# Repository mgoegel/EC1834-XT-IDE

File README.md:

# XT-IDE 8-Bit IDE Controller for Robotron EC1834

[Deutsche Version](README-DE.md)

This is a modified version of the original Glitchworks XT-IDE rev 4 controller.

The ISA edge connector is replaced with DIN 41612 connector, used by the Robotron EC1834 PC.

Also the layout of the PCB was modified, to fit the mounting height.

Modification was done by Mario Goegel.

**IMPORTANT NOTES ON Rev 4b (Revision not printed)**

The idea to change the pull down resistors to pull up was an bad idea, as I did not saw all required changes.
The board will just not work, if assembled as planned.

Required changes:

* Pin 2 from RN2 has to be disconnected
* A 10K resistor needs to be connected on U1 pin 12 and GND (may be C1)
* The descriptions are not correct for SW2 ENA and WR - they match the original version, as they are not connected to RP2
* SW2 8K might be out of function - and 28C256 ROMs might not work. Untested, 82C64B are fine.

Fixed in revision 4c

**Disclaimer:**

I don't take responsibility for any damages resulting from these modifications. All changes have been made with the best of intentions and to the best of my knowledge.
Use on your own risk!

Original text from Glitchworks (modified):

[Glitch Works](http://www.glitchwrks.com/) continuing extension of the XT-IDE rev 2 ISA controller. This board, when used with a custom BIOS like the XT-IDE Universal BIOS, allows the use of modern 16-bit IDE devices on the 8-bit ISA bus.

More info on the Glitch Works project to provide boards, kits, and fully assembled units [can be found here](http://www.glitchwrks.com/xt-ide). A writeup on the rev 4 design process [is available here](http://www.glitchwrks.com/2017/11/23/xt-ide-rev4). 

Except for the DIN 41612 connector.

If you're looking for the rev 3 branch, [it can be found here](https://github.com/glitchwrks/xt_ide/tree/rev_3). The README and related documentation have been preserved along with the design files.

### Jumper Settings

[modem7](http://minuszerodegrees.net/) created a great set of jumper diagrams for the rev 4 boards, available [on his site](http://www.minuszerodegrees.net/xtide/rev_4/XT-IDE%20Rev%204%20-%20general.htm).

### Bill of Materials

You can find a BOM with Mouser part numbers [here](https://github.com/glitchwrks/xt_ide/blob/master/bill_of_materials.md). Do note that you can purchase complete parts kits from [The Glitch Works](http://www.glitchwrks.com/xt-ide) in addition to bare PC boards.

### Slot 8 Support

Completely removed in this version!

### Contributors

* Mario Goegel: Modification for EC1834
* Scott Christensen: inspriation 16-bit ATA interface for the 8-bit ISA bus
* Jeff Leyda/Hargle: original production board work, original BIOS work
* Andrew Lynch/N8VEM: layout work, initial group buy(s) on earlier revisions
* modem7: documentation, switch/jumper drawings

**Please contact me or send a pull request to get your name added to the list!**

There were no authors/contributors listed in the XT-IDE rev 2 schematics/board layout I started with. If you have contributed to this project and would like your name here, on the schematic, or on the board layout, please let me know. You can open an issue or submit a pull request.

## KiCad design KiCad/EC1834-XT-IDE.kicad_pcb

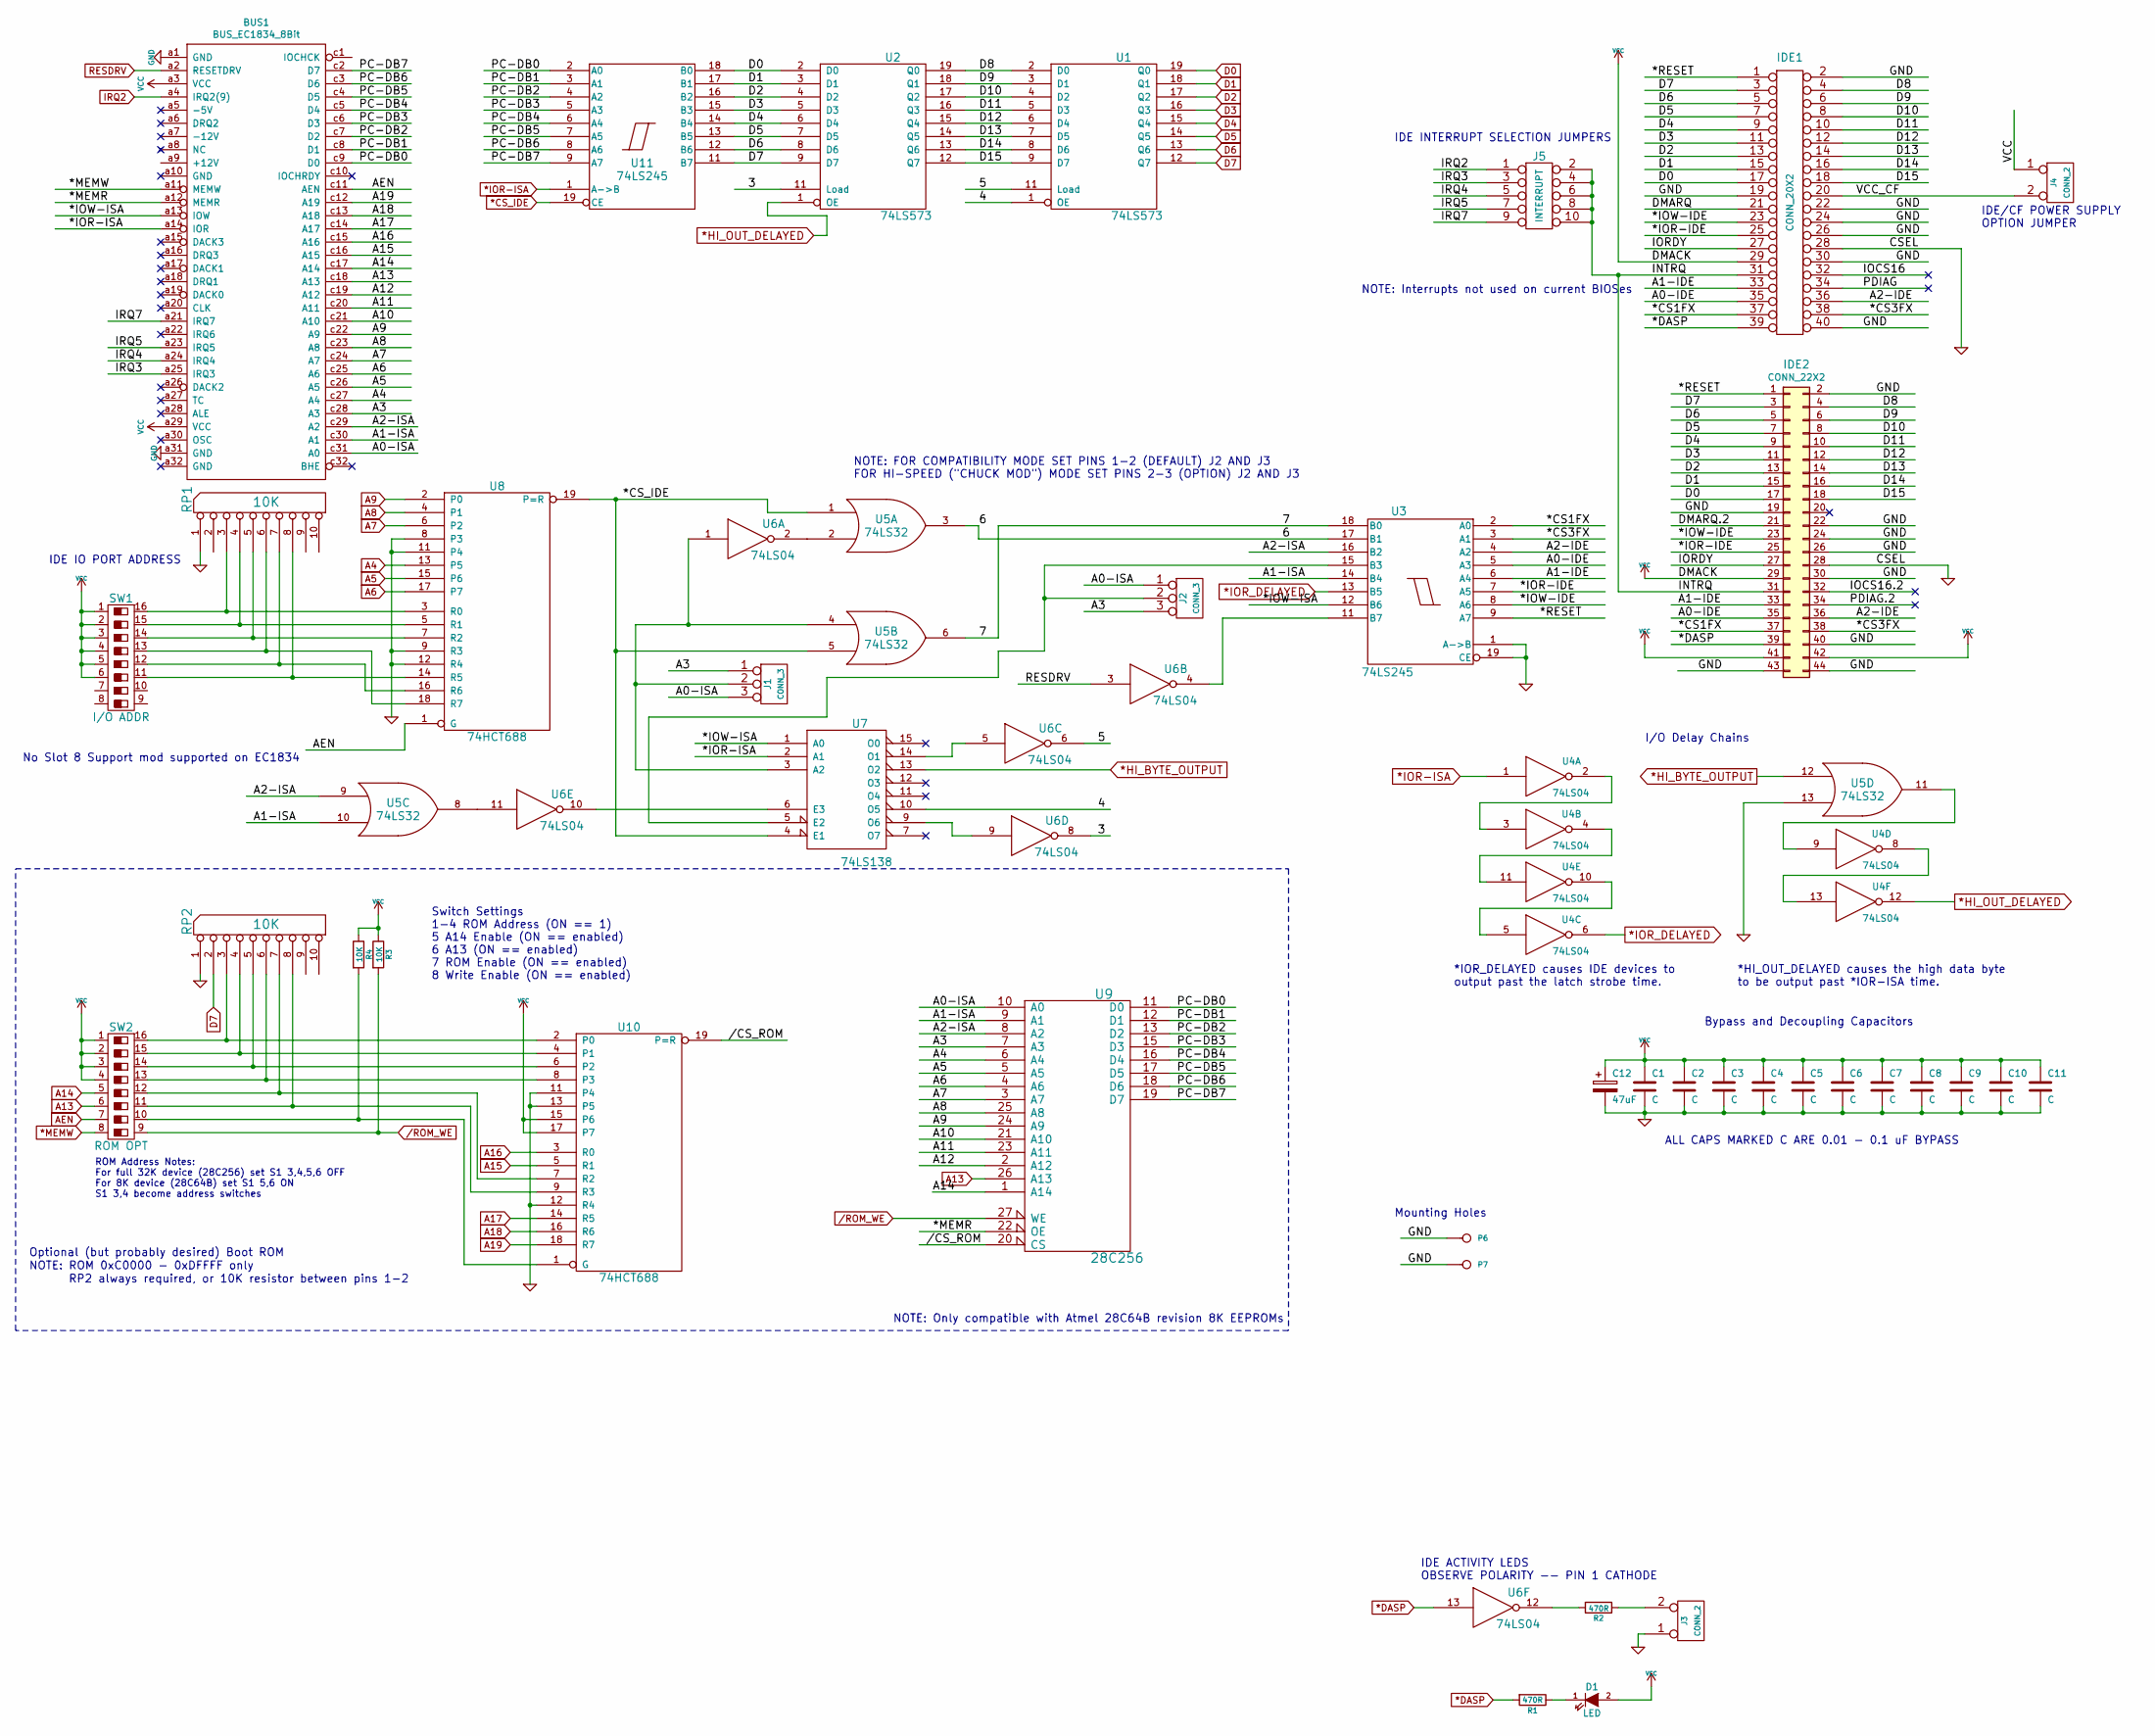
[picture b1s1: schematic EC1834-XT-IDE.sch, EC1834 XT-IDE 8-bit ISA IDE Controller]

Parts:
BUS1: BUS_EC1834_8Bit; DIN41612_C_3x32_Male_Horizontal_THT
C1, C2, C3, C4, C5, C6, C7, C8, C10, C11: C; AX_300
C9: C; AX_400
C12: 47uF; CP_RAD_250_100
D1: LED; LED-5MM
IDE1: CONN_20X2; STRAIGHT_2x20
IDE2: CONN_22X2; PinSocket_2x22_P2.00mm_Horizontal
J1, J2: CONN_3; 1x3
J3, J4: CONN_2; 1x2
J5: INTERRUPT; 5x2
P6, P7: CONN_1; 120mil_no_silkscreen
R1, R2: 470R; AX_400
R3, R4: 10K; AX_400
RP1, RP2: 10K; SIP10
SW1: I/O ADDR; DIP-16_300_OBROUND_NO_NOTCH
SW2: ROM OPT; DIP-16_300_OBROUND_NO_NOTCH
U1, U2: 74LS573; DIP-20_300_OBROUND
U3, U11: 74LS245; DIP-20_300_OBROUND
U4, U6: 74LS04; DIP-14_300_OBROUND
U5: 74LS32; DIP-14_300_OBROUND
U7: 74LS138; DIP-16_300_OBROUND
U8, U10: 74HCT688; DIP-20_300_OBROUND
U9: 28C256; DIP-28_600_OBROUND

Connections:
*CS_IDE: U5.1, U5.5, U7.4 (E1), U8.19 (P=R), U11.19 (CE)
*DASP: IDE1.39, IDE2.39, R1.2, U6.13
*HI_BYTE_OUTPUT: U5.12, U7.13 (O2)
*HI_OUT_DELAYED: U2.1 (OE), U4.12
*IOR-ISA: BUS1.a14 (IOR), U4.1, U7.2 (A1), U11.1 (A->B)
*IOR_DELAYED: U3.13 (B5), U4.6
*MEMW: BUS1.a11 (MEMW), SW2.8
/3: U2.11 (Load), U6.8
/4: U1.1 (OE), U7.10 (O5)
/5: U1.11 (Load), U6.6
/6: U3.17 (B1), U5.3
/7: U3.18 (B0), U5.6
/*CS1FX: IDE1.37, IDE2.37, U3.2 (A0)
/*CS3FX: IDE1.38, IDE2.38, U3.3 (A1)
/*IOR-IDE: IDE1.25, IDE2.25, U3.7 (A5)
/*IOW-IDE: IDE1.23, IDE2.23, U3.8 (A6)
/*IOW-ISA: BUS1.a13 (IOW), U3.12 (B6), U7.1 (A0)
/*MEMR: BUS1.a12 (MEMR), U9.22 (OE)
/*RESET: IDE1.1, IDE2.1, U3.9 (A7)
//CS_ROM: U9.20 (CS), U10.19 (P=R)
/A0-IDE: IDE1.35, IDE2.35, U3.5 (A3)
/A0-ISA: BUS1.c31 (A0), J1.3, J2.1, U9.10 (A0)
/A1-IDE: IDE1.33, IDE2.33, U3.6 (A4)
/A1-ISA: BUS1.c30 (A1), U3.14 (B4), U5.10, U9.9 (A1)
/A2-IDE: IDE1.36, IDE2.36, U3.4 (A2)
/A2-ISA: BUS1.c29 (A2), U3.16 (B2), U5.9, U9.8 (A2)
/A3: BUS1.c28 (A3), J1.1, J2.3, U9.7 (A3)
/A10: BUS1.c21 (A10), U9.21 (A10)
/A11: BUS1.c20 (A11), U9.23 (A11)
/A12: BUS1.c19 (A12), U9.2 (A12)
/D8: IDE1.4, IDE2.4, U1.2 (D0), U2.19 (Q0)
/D9: IDE1.6, IDE2.6, U1.3 (D1), U2.18 (Q1)
/D10: IDE1.8, IDE2.8, U1.4 (D2), U2.17 (Q2)
/D11: IDE1.10, IDE2.10, U1.5 (D3), U2.16 (Q3)
/D12: IDE1.12, IDE2.12, U1.6 (D4), U2.15 (Q4)
/D13: IDE1.14, IDE2.14, U1.7 (D5), U2.14 (Q5)
/D14: IDE1.16, IDE2.16, U1.8 (D6), U2.13 (Q6)
/D15: IDE1.18, IDE2.18, U1.9 (D7), U2.12 (Q7)
/DMARQ: IDE1.21
/DMARQ.2: IDE2.21
/INTRQ: IDE1.31, IDE2.31, J5.2, J5.4, J5.6, J5.8, J5.10
/IOCS16: IDE1.32
/IOCS16.2: IDE2.32
/IORDY: IDE1.27, IDE2.27
/IRQ3: BUS1.a25 (IRQ3), J5.3
/IRQ4: BUS1.a24 (IRQ4), J5.5
/IRQ5: BUS1.a23 (IRQ5), J5.7
/IRQ7: BUS1.a21 (IRQ7), J5.9
/PC-DB0: BUS1.c9 (D0), U9.11 (D0), U11.2 (A0)
/PC-DB1: BUS1.c8 (D1), U9.12 (D1), U11.3 (A1)
/PC-DB2: BUS1.c7 (D2), U9.13 (D2), U11.4 (A2)
/PC-DB3: BUS1.c6 (D3), U9.15 (D3), U11.5 (A3)
/PC-DB4: BUS1.c5 (D4), U9.16 (D4), U11.6 (A4)
/PC-DB5: BUS1.c4 (D5), U9.17 (D5), U11.7 (A5)
/PC-DB6: BUS1.c3 (D6), U9.18 (D6), U11.8 (A6)
/PC-DB7: BUS1.c2 (D7), U9.19 (D7), U11.9 (A7)
/PDIAG: IDE1.34
/PDIAG.2: IDE2.34
/ROM_WE: R3.2, SW2.9, U9.27 (WE)
/VCC_CF: IDE1.20, J4.2 (PM)
A4: BUS1.c27 (A4), U8.13 (P5), U9.6 (A4)
A5: BUS1.c26 (A5), U8.15 (P6), U9.5 (A5)
A6: BUS1.c25 (A6), U8.17 (P7), U9.4 (A6)
A7: BUS1.c24 (A7), U8.6 (P2), U9.3 (A7)
A8: BUS1.c23 (A8), U8.4 (P1), U9.25 (A8)
A9: BUS1.c22 (A9), U8.2 (P0), U9.24 (A9)
A13: BUS1.c18 (A13), SW2.6, U9.26 (A13)
A14: BUS1.c17 (A14), SW2.5, U9.1 (A14)
A15: BUS1.c16 (A15), U10.5 (R1)
A16: BUS1.c15 (A16), U10.3 (R0)
A17: BUS1.c14 (A17), U10.14 (R5)
A18: BUS1.c13 (A18), U10.16 (R6)
A19: BUS1.c12 (A19), U10.18 (R7)
AEN: BUS1.c11 (AEN), SW2.7, U8.1 (G)
D0: IDE1.17, IDE2.17, U1.19 (Q0), U2.2 (D0), U11.18 (B0)
D1: IDE1.15, IDE2.15, U1.18 (Q1), U2.3 (D1), U11.17 (B1)
D2: IDE1.13, IDE2.13, U1.17 (Q2), U2.4 (D2), U11.16 (B2)
D3: IDE1.11, IDE2.11, U1.16 (Q3), U2.5 (D3), U11.15 (B3)
D4: IDE1.9, IDE2.9, U1.15 (Q4), U2.6 (D4), U11.14 (B4)
D5: IDE1.7, IDE2.7, U1.14 (Q5), U2.7 (D5), U11.13 (B5)
D6: IDE1.5, IDE2.5, U1.13 (Q6), U2.8 (D6), U11.12 (B6)
D7: IDE1.3, IDE2.3, RP2.2, U1.12 (Q7), U2.9 (D7), U11.11 (B7)
GND: BUS1.a1 (GND), BUS1.a31 (GND), C1.2, C2.2, C3.2, C4.2, C5.2, C6.2, C7.2, C8.2, C9.2, C10.2, C11.2, C12.2, IDE1.2, IDE1.19, IDE1.22, IDE1.24, IDE1.26, IDE1.28, IDE1.30, IDE1.40, IDE2.2, IDE2.19, IDE2.22, IDE2.24, IDE2.26, IDE2.28, IDE2.30, IDE2.40, IDE2.43, IDE2.44, J3.1, P6.1, P7.1, RP1.1 (COM), RP2.1 (COM), U1.10 (GND), U2.10 (GND), U3.1 (A->B), U3.10 (GND), U3.19 (CE), U4.7 (GND), U5.7 (GND), U5.13, U6.7 (GND), U7.8 (GND), U8.8 (P3), U8.9 (R3), U8.10 (GND), U8.11 (P4), U8.12 (R4), U9.14 (GND), U10.10 (GND), U10.11 (P4), U10.12 (R4), U10.13 (P5), U11.10 (GND)
IRQ2: BUS1.a4 (IRQ2(9)), J5.1
unnamed: D1.1 (K), R1.1
unnamed: J1.2 (PM), U5.4, U6.1, U7.3 (A2)
unnamed: J2.2 (PM), U3.15 (B3), U7.5 (E2)
unnamed: J3.2 (PM), R2.1
unnamed: R2.2, U6.12
unnamed: R4.2, SW2.10, U10.1 (G)
unnamed: RP1.3, SW1.16, U8.3 (R0)
unnamed: RP1.4, SW1.15, U8.5 (R1)
unnamed: RP1.5, SW1.14, U8.7 (R2)
unnamed: RP1.6, SW1.13, U8.18 (R7)
unnamed: RP1.7, SW1.12, U8.16 (R6)
unnamed: RP1.8, SW1.11, U8.14 (R5)
unnamed: RP2.3, SW2.16, U10.2 (P0)
unnamed: RP2.4, SW2.15, U10.4 (P1)
unnamed: RP2.5, SW2.14, U10.6 (P2)
unnamed: RP2.6, SW2.13, U10.8 (P3)
unnamed: RP2.7, SW2.12, U10.7 (R2)
unnamed: RP2.8, SW2.11, U10.9 (R3)
unnamed: U3.11 (B7), U6.4
unnamed: U4.2, U4.3
unnamed: U4.9, U5.11
unnamed: U4.5, U4.10
unnamed: U4.4, U4.11
unnamed: U4.8, U4.13
unnamed: U5.2, U6.2
unnamed: U5.8, U6.11
unnamed: U6.5, U7.14 (O1)
unnamed: U6.9, U7.9 (O6)
unnamed: U6.10, U7.6 (E3)
RESDRV: BUS1.a2 (RESETDRV), U6.3
VCC: BUS1.a3 (VCC), BUS1.a29 (VCC), C1.1, C2.1, C3.1, C4.1, C5.1, C6.1, C7.1, C8.1, C9.1, C10.1, C11.1, C12.1, D1.2 (A), IDE1.29, IDE2.29, IDE2.41, IDE2.42, J4.1, R3.1, R4.1, SW1.1, SW1.2, SW1.3, SW1.4, SW1.5, SW1.6, SW2.1, SW2.2, SW2.3, SW2.4, U1.20 (VCC), U2.20 (VCC), U3.20 (VCC), U4.14 (VCC), U5.14 (VCC), U6.14 (VCC), U7.16 (VCC), U8.20 (VCC), U9.28 (VCC), U10.15 (P6), U10.17 (P7), U10.20 (VCC), U11.20 (VCC)

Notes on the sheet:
IDE/CF POWER SUPPLY OPTION JUMPER
IDE ACTIVITY LEDS OBSERVE POLARITY -- PIN 1 CATHODE
IDE INTERRUPT SELECTION JUMPERS
IDE IO PORT ADDRESS
NOTE: FOR COMPATIBILITY MODE SET PINS 1-2 (DEFAULT) J2 AND J3 FOR HI-SPEED ("CHUCK MOD") MODE SET PINS 2-3 (OPTION) J2 AND J3
NOTE: Only compatible with Atmel 28C64B revision 8K EEPROMs
NOTE: ROM 0xC0000 - 0xDFFFF only
Switch Settings 1-4 ROM Address (ON == 1) 5 A14 Enable (ON == enabled) 6 A13 (ON == enabled) 7 ROM Enable (ON == enabled) 8 Write Enable (ON == enabled)
ROM Address Notes: For full 32K device (28C256) set S1 3,4,5,6 OFF For 8K device (28C64B) set S1 5,6 ON S1 3,4 become address switches
Optional (but probably desired) Boot ROM
Mounting Holes
Bypass and Decoupling Capacitors
RP2 always required, or 10K resistor between pins 1-2
NOTE: Interrupts not used on current BIOSes
ALL CAPS MARKED C ARE 0.01 - 0.1 uF BYPASS
I/O Delay Chains
*IOR_DELAYED causes IDE devices to output past the latch strobe time.
*HI_OUT_DELAYED causes the high data byte to be output past *IOR-ISA time.
No Slot 8 Support mod supported on EC1834

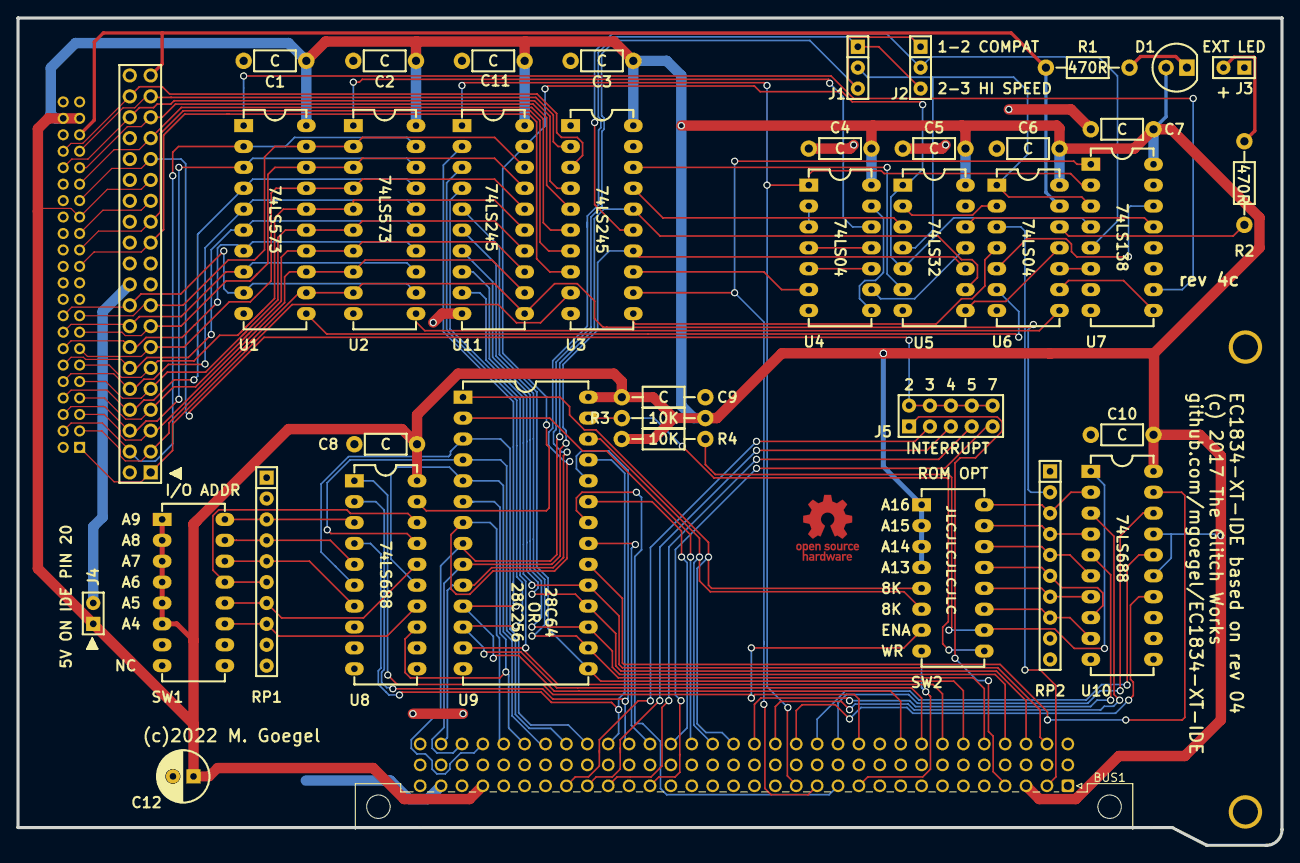
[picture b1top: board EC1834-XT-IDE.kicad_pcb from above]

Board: 2 copper layers, 153.7 x 100.6 mm, 42 parts (0 on the bottom side), 109 nets.

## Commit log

2022-04-15 Moved some tracks to move drill holes for new slot sheet position in EC1834
2022-04-19 Moved some ICs Prepared new arrangement
2022-05-21 Reorganzied KiCad project Completed PCB, added some configuration notes on PCB
2022-07-11 Added doc in German Added information about issues and how to solve
2022-07-11 doc improvement
2022-07-29 Updated schema revision Updated gerber files Added default BIOS

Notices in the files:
KiCad/EC1834-XT-IDE.kicad_pcb:
(c)2022 M. Goegel
(c) 2017 The Glitch Works
